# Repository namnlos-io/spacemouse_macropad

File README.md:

# SpaceMouse® Compact MacroPad

A macro pad for 3DConnexion SpaceMouse® Compact based on ["Spacemouse Wireless MacroPad"](https://www.thingiverse.com/thing:3562600)
by [Arron Craig](https://www.thingiverse.com/ajcraig).

## License

This work is licensed under a [Creative Commons Attribution-NonCommercial 4.0 International License](http://creativecommons.org/licenses/by-nc/4.0/).

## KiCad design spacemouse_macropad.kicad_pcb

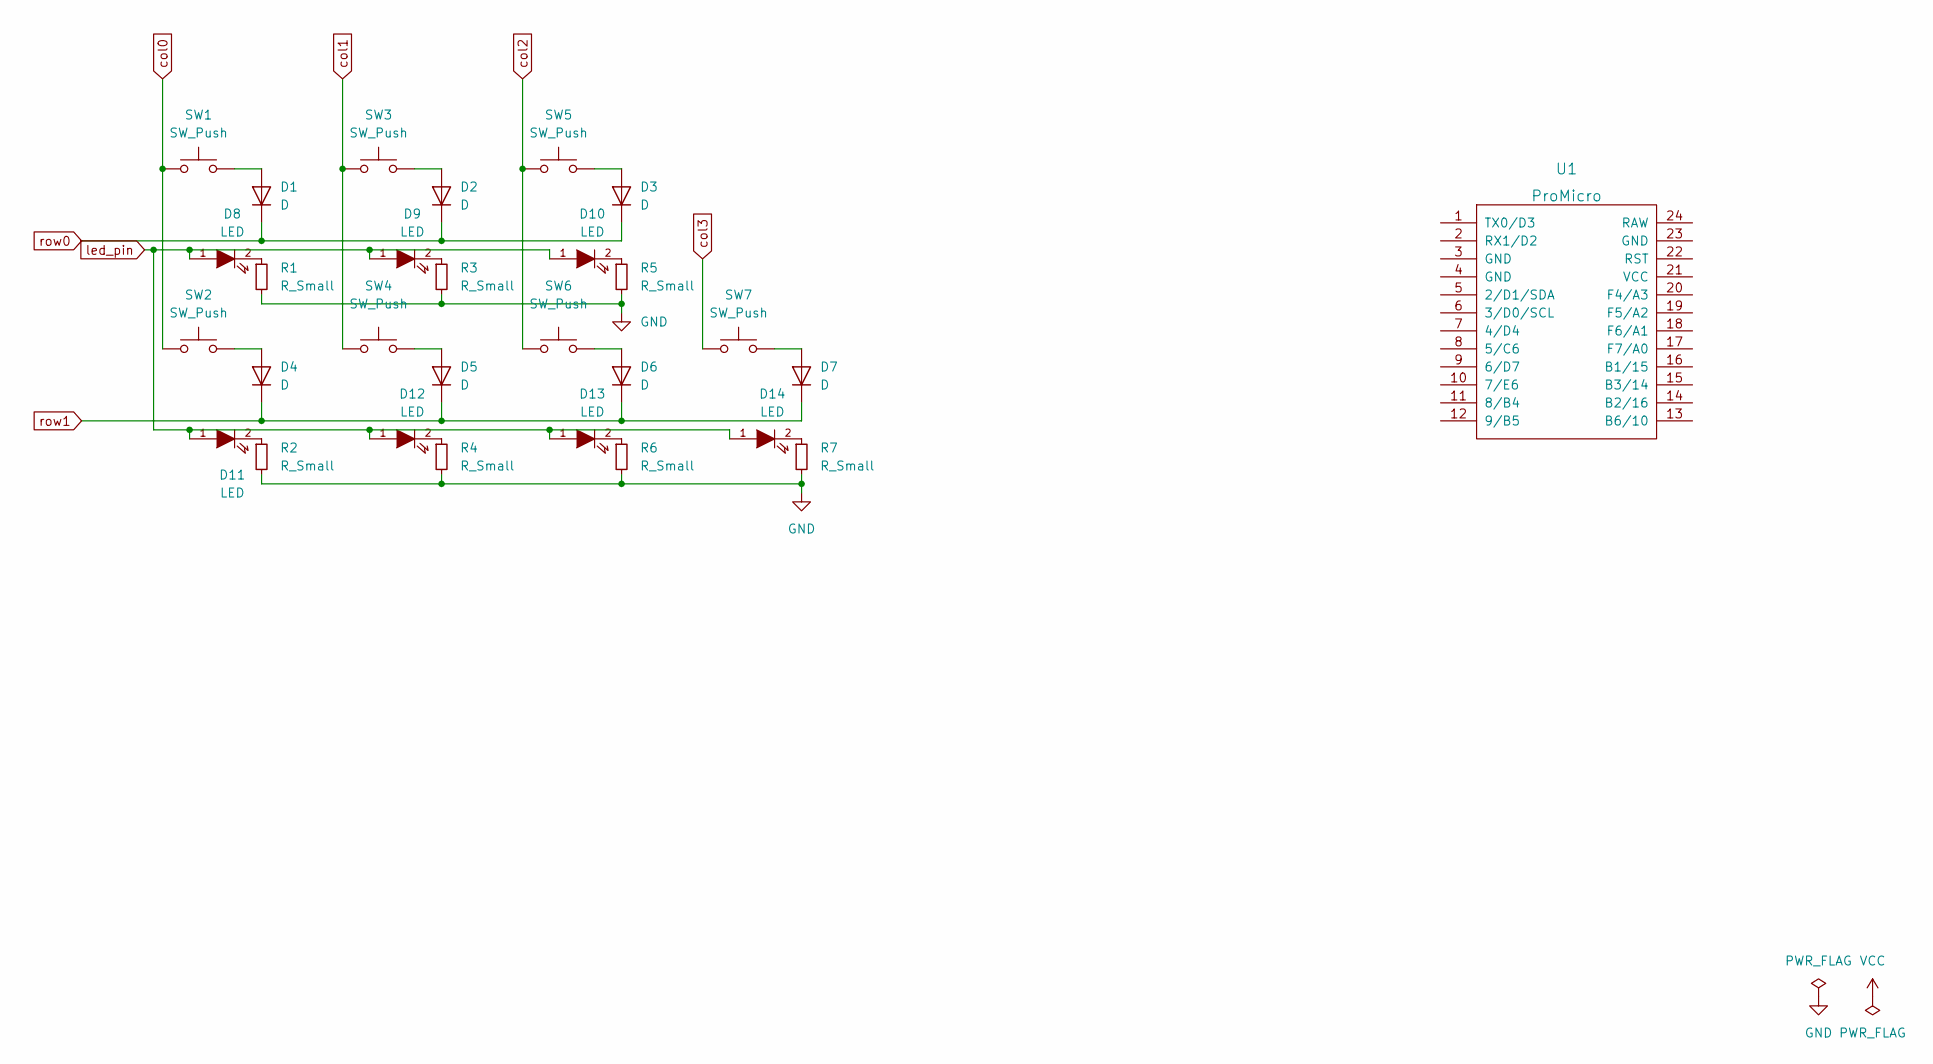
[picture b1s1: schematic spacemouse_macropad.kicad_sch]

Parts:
D1, D2, D3, D4, D5, D6, D7: D; Diode-Hybrid-Back
D8, D9, D10, D11, D12, D13, D14: LED; LED_3mm
R1, R2, R3, R4, R5, R6, R7: R_Small; Resistor-Hybrid-Back
SW1, SW2, SW3, SW4, SW5, SW6, SW7: SW_Push; MX-Alps-Choc-1U
U1: ProMicro; ProMicro_v2

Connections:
GND: R1.2, R2.2, R3.2, R4.2, R5.2, R6.2, R7.2
unnamed: D3.2 (A), SW5.2
unnamed: D4.2 (A), SW2.2
unnamed: D8.2 (K), R1.1
unnamed: D9.2 (K), R3.1
unnamed: D10.2 (K), R5.1
unnamed: D11.2 (K), R2.1
unnamed: D12.2 (K), R4.1
unnamed: D13.2 (K), R6.1
unnamed: D14.2 (K), R7.1
unnamed: D1.2 (A), SW1.2
unnamed: D2.2 (A), SW3.2
unnamed: D5.2 (A), SW4.2
unnamed: D6.2 (A), SW6.2
unnamed: D7.2 (A), SW7.2
col0: SW1.1, SW2.1
col1: SW3.1, SW4.1
col2: SW5.1, SW6.1
col3: SW7.1
led_pin: D8.1 (A), D9.1 (A), D10.1 (A), D11.1 (A), D12.1 (A), D13.1 (A), D14.1 (A)
row0: D1.1 (K), D2.1 (K), D3.1 (K)
row1: D4.1 (K), D5.1 (K), D6.1 (K), D7.1 (K)

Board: 2 copper layers, 29 parts (0 on the bottom side), 21 nets, no tracks yet.

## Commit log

2022-05-15 Initial commit.
2022-07-02 A start.
